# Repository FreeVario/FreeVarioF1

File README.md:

## Welcome to FreeVario

Freevario is an opensource device to provides telemetry data to any vario based program such as XCSoar or XCTrack via bluetooth or wifi. It is based on de STM32F3 processor. The project includes the board Eagle design and source code.
The current status of the project is beta, it is 100% usable, just some rough edges here and there. Since the paragliding season is active, only bug fixes will be added. 

### Features:

Bluetooth, Serial or USB OTG streaming<br>
Solar charger <br>
Power bank (200mA) <br>
Power passthru from external supply <br>
Interval powerbank<br>
Dual pressure sensor support <br>
Adaptive Vario* <br>
Humidity sensor <br>
Accelerometer<br>
Piezo speaker for vario audio <br>
Serial GPS NMEA <br>
NMEA Output PCProbe, PTAS1 and LXNAV<br>

*Adaptive Vario: The sensitivity filter of the barometric sensors are adapted according to the environment. Eg. On a quiet day your flight will be more stable, causing the filter to become more sensitive to changes, this way you will be able to detect the lighter thermals.

#### Bluetooth, Serial or USB OTG streaming

Multiple options available. You can mount a HM-13 bluetooth module to stream BLE or standard bluetooth. Internal serial port can either be used for a i2c OLED display or as an internal serial port for built-in solutions like a Kobo reader.

#### Solar charger

The on board lipo charger can handle multiple power sources including a solar panel to extend the battery life.

#### Powerbank

A on board powerbank can supply up to 200mA 5V via the USB cable to any connected device. When the device is connected to a charger, it will activate a pass through circuit so that the connected device is also charged. This way, disconnecting the usb cable won’t be necessary.
Another option is interval power supply. This will deliver 1 minute out of 5 minutes to the connected device. Most devices won’t support this however. You will need a custom kernel for some Android devices. But is does work with Kobo devices and XCSoar (Top Hat) or LK8000.

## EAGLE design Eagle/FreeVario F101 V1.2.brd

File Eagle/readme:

Eagle files for the FreeVario board

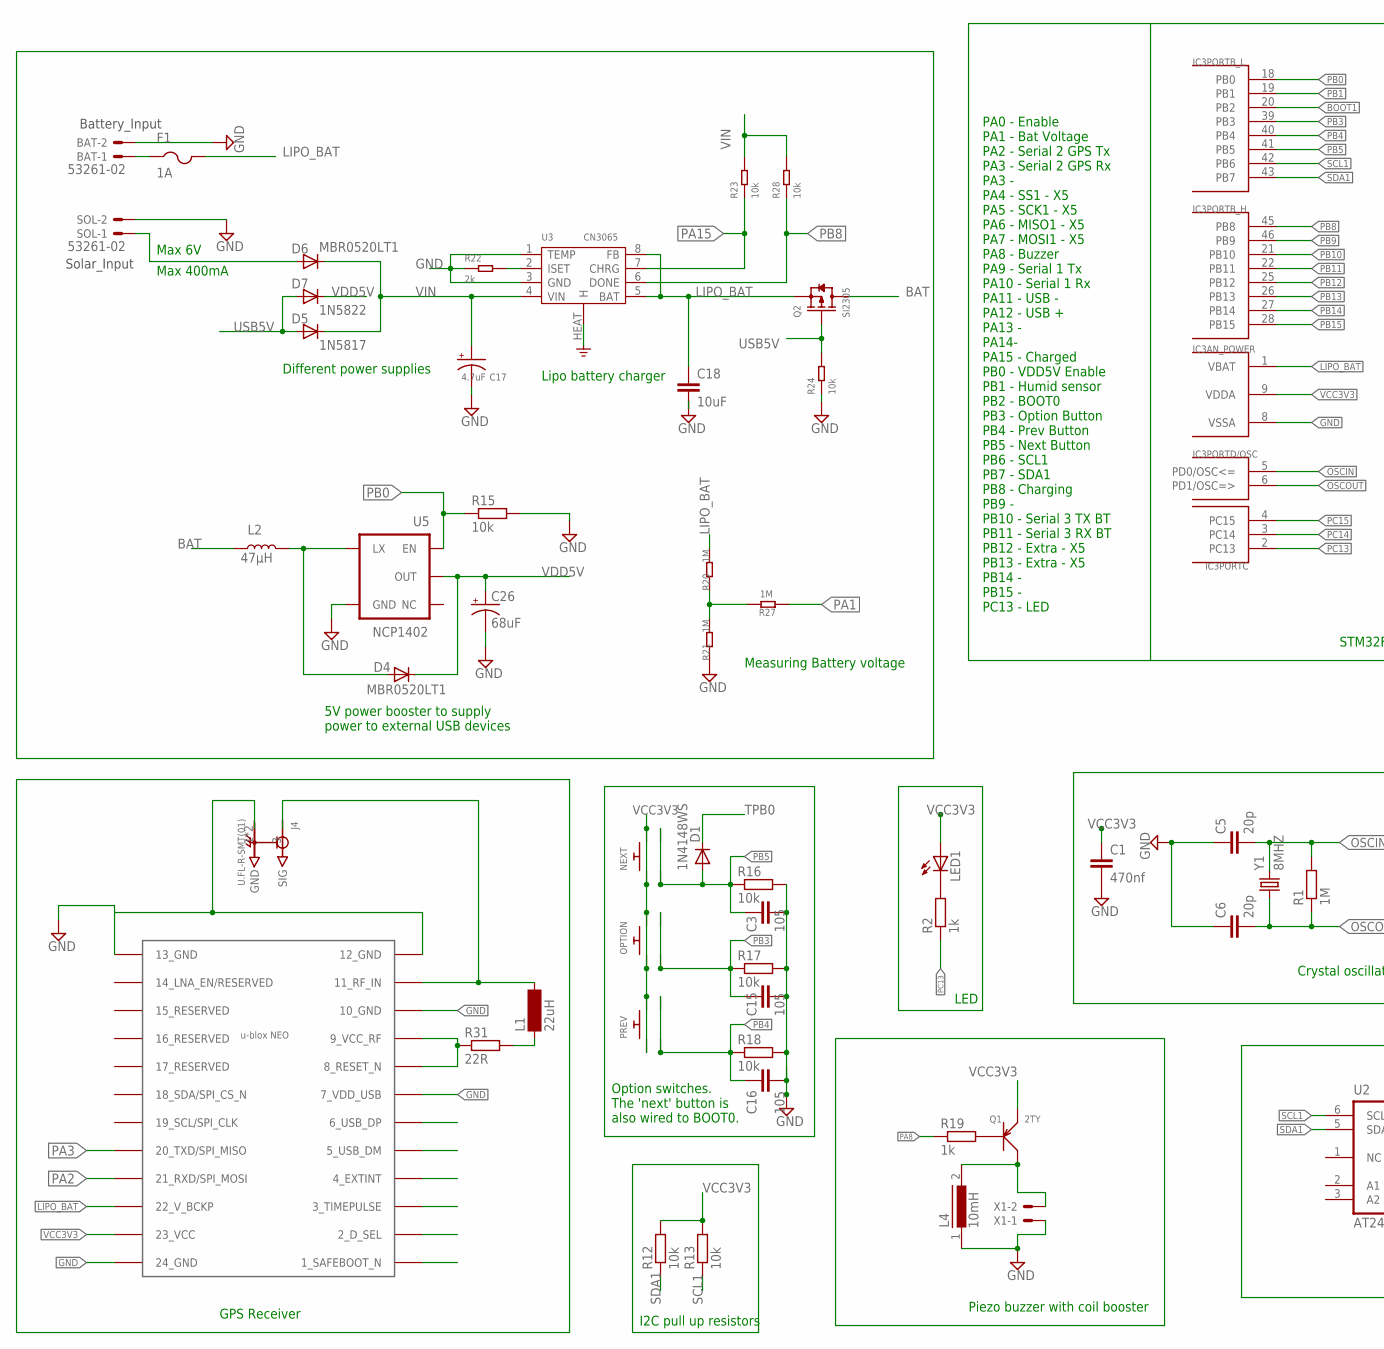
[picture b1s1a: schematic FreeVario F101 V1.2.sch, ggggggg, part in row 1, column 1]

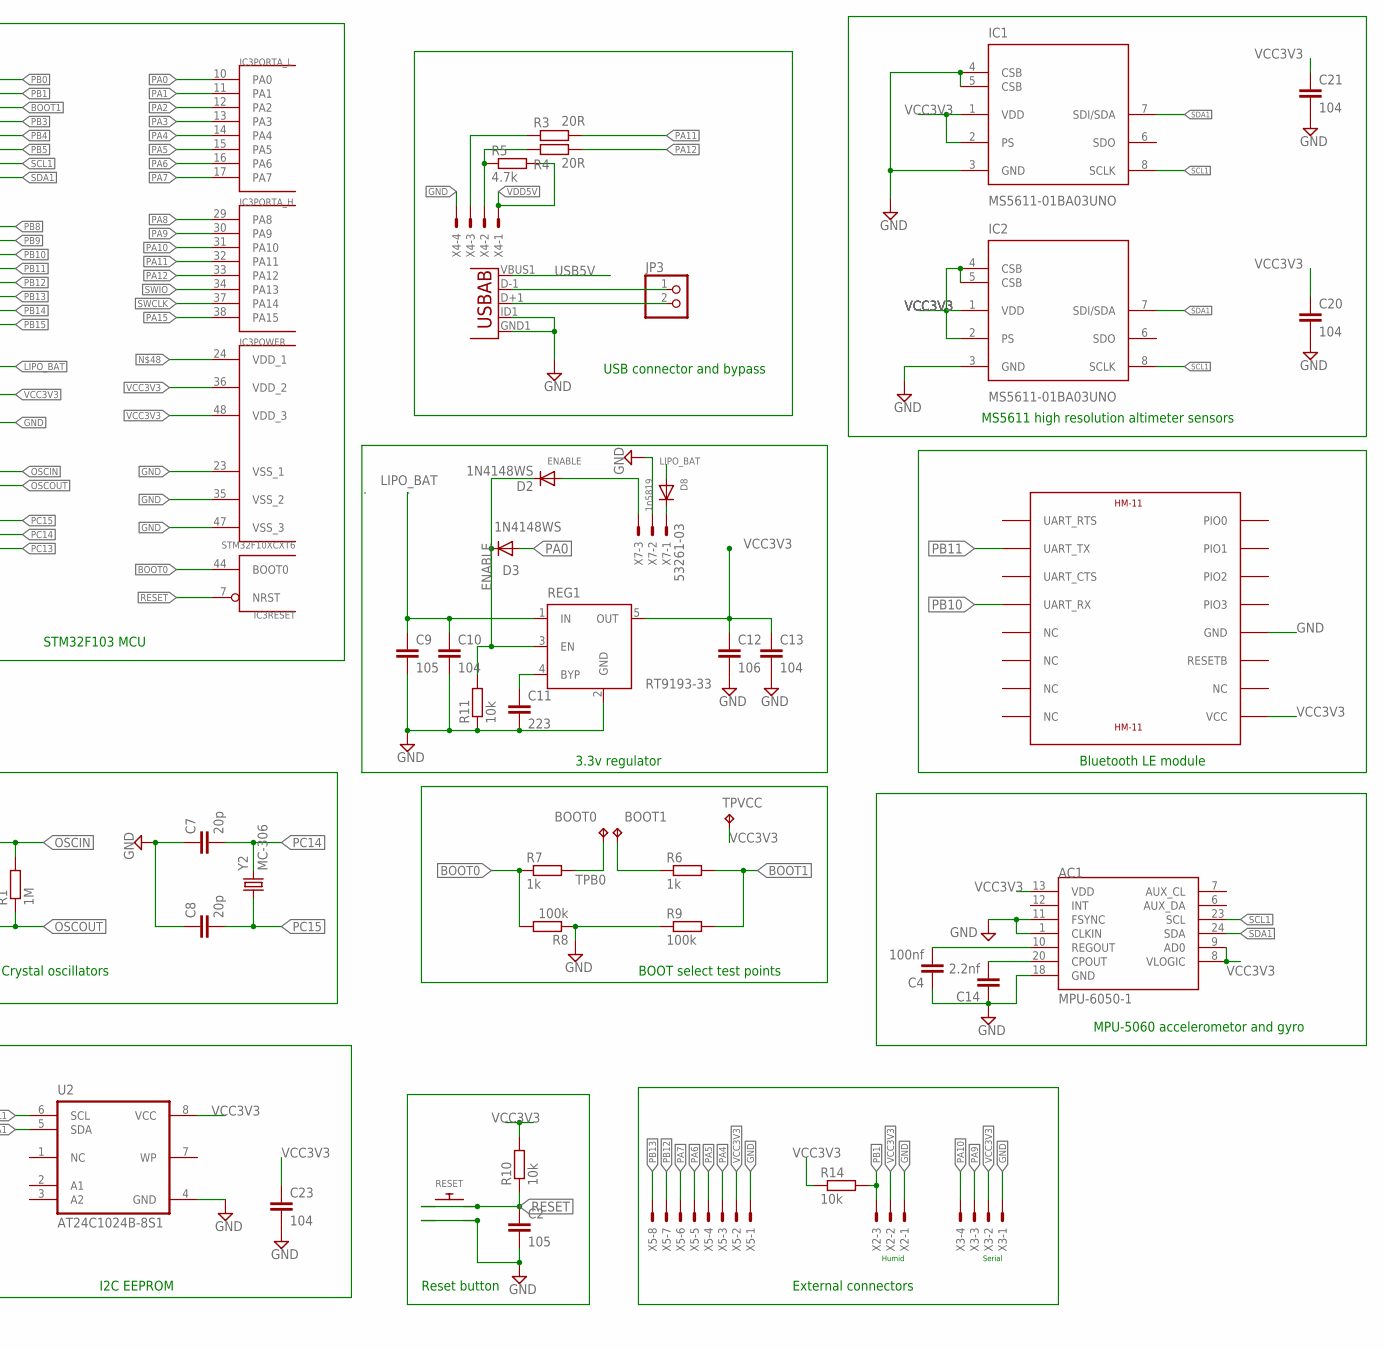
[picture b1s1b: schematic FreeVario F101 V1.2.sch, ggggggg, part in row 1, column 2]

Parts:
AC1: MPU-6050-1; QFN-24-4MM2
BAT: 53261-02
BOOT0, BOOT1: TPTP08R; TP08R
C1: 470nf; C0603K
C2, C3, C15, C16: 105; C0603
C4: 100nf; C0603K
C5, C6, C7, C8: 20p; C0603K
C9: 105; C0603K
C10, C13, C20, C21, C23: 104; C0603K
C11: 223; C0603K
C12: 106; C0603K
C14: 2.2nf; C0603K
C17: 4.7uF; EIA3216
C18: 10uF; C0805
C26: 68uF; EIA3528
D1, D2, D3: 1N4148WS; SOD323-R
D4, D6: MBR0520LT1; SOD-123
D5: 1N5817; SOD-123
D7: 1N5822; DO-214AC
D8: 1n5819; SOD-123
F1: 1A; R1206
HM13: HM-11
IC1, IC2: MS5611-01BA03UNO; SON125P300X500X100-8N
IC3: STM32F10XCXT6; TQFP48
J4: U.FL-R-SMT(01); HRS_U.FL-R-SMT(01)
JP3: PINHD-1X2; 1X02
L1: 22uH; SM-1206
L2: 47µH; CR54
L4: 10mH; MMICC7
LED1: LEDCHIP-LED0603; CHIP-LED0603
NEXT: TS-015A
OPTION: TS-015A
PREV: TS-015A
Q1: 2TY; SOT-23
Q2: SI2305; SOT-23
R1: 1M; R0603
R2, R6, R7, R19: 1k; R0603
R3, R4: 20R; R0603
R5: 4.7k; R0603
R8, R9: 100k; R0603
R10, R11, R12, R13, R14, R15, R16, R17, R18, R23, R24, R28: 10k; R0603
R20, R21, R27: 1M; 0603
R22: 2k; R0603
R31: 22R; R0603
REG1: RT9193-33; SOT23-5
RESET: TS-015A
SOL: 53261-02
TPVCC: TPTP08SQ; TP08SQ
U1: USB""; USB-MICRO-SMD
U2: AT24C1024B-8S1; SO08-8S1
U3: CN3065; DFN-8
U4: NEO-M8
U5: NCP1402; SOT23-5
X1: 53261-02
X2, X7: 53261-03
X3, X4: 53261-04
X5: 53261-08
Y1: 8MHZ; SM49
Y2: MC-306

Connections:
BAT: L2.P$1 (1), Q2.3 (D)
BOOT0: IC3.44 (BOOT0), R7.1, R8.2
BOOT1: IC3.20 (PB2), R6.2, R9.2
ENABLE: D2.C, D3.C, R11.2, REG1.3 (EN)
GND: AC1.1 (CLKIN), AC1.11 (FSYNC), AC1.18 (GND), BAT.2, C1.2, C2.2, C3.2, C4.1, C5.1, C6.1, C7.1, C8.1, C9.2, C10.2, C11.2, C12.2, C13.2, C14.1, C15.2, C16.2, C17.-, C18.2, C20.2, C23.2, C26.C (-), HM13.GND, IC1.3 (GND), IC1.4 (CSB), IC1.5 (CSB), IC2.3 (GND), IC3.8 (VSSA), IC3.23 (VSS_1), IC3.35 (VSS_2), IC3.47 (VSS_3), J4.1 (GND), J4.2 (GND), L4.1, R8.1, R9.1, R11.1, R15.2, R16.2, R17.2, R18.2, R21.1, R22.1, R24.1, REG1.2 (GND), RESET.P$2, RESET.P$4, SOL.2, U1.GND1 (GND), U1.ID1 (USBID), U2.4 (GND), U3.1 (TEMP), U3.3 (GND), U3.HEAT (H), U4.7 (7_VDD_USB), U4.10 (10_GND), U4.12 (12_GND), U4.13 (13_GND), U4.24 (24_GND), U5.4 (GND), X1.1, X2.1, X3.1, X4.4, X5.1, X7.2
LIPO_BAT: C9.1, C10.1, C18.1, D8.A, F1.2, IC3.1 (VBAT), Q2.2 (S), R20.2, REG1.1 (IN), U3.5 (BAT), U3.8 (FB), U4.22 (22_V_BCKP)
unnamed: D8.C, X7.1
unnamed: LED1.C, R2.2
unnamed: C11.1, REG1.4 (BYP)
unnamed: R3.1, X4.3
unnamed: R4.1, R5.1, X4.2
unnamed: BAT.1, F1.1
unnamed: BOOT1.TP, R6.1
unnamed: R20.1, R21.2, R27.2
unnamed: D2.A, X7.3
unnamed: Q1.1 (B), R19.2
unnamed: D6.A, SOL.1
unnamed: AC1.10 (REGOUT), C4.2
unnamed: R22.2, U3.2 (ISET)
unnamed: AC1.20 (CPOUT), C14.2
unnamed: L4.2, Q1.3 (C), X1.2
unnamed: JP3.1, U1.D-1 (D-)
unnamed: JP3.2, U1.D+1 (D+)
unnamed: D4.A, L2.P$2 (2), U5.5 (LX)
unnamed: J4.3 (SIG), L1.2, U4.11 (11_RF_IN)
unnamed: L1.1, R31.2
unnamed: R31.1, U4.8 (8_RESET_N), U4.9 (9_VCC_RF)
OSCIN: C5.2, IC3.5 (PD0/OSC<=), R1.2, Y1.2
OSCOUT: C6.2, IC3.6 (PD1/OSC=>), R1.1, Y1.1
PA0: D3.A, IC3.10 (PA0)
PA1: IC3.11 (PA1), R27.1
PA2: IC3.12 (PA2), U4.21 (21_RXD/SPI_MOSI)
PA3: IC3.13 (PA3), U4.20 (20_TXD/SPI_MISO)
PA4: IC3.14 (PA4), X5.3
PA5: IC3.15 (PA5), X5.4
PA6: IC3.16 (PA6), X5.5
PA7: IC3.17 (PA7), X5.6
PA8: IC3.29 (PA8), R19.1
PA9: IC3.30 (PA9), X3.3
PA10: IC3.31 (PA10), X3.4
PA11: IC3.32 (PA11), R3.2
PA12: IC3.33 (PA12), R4.2
PA15: IC3.38 (PA15), R23.1, U3.7 (CHRG)
PB0: IC3.18 (PB0), R15.1, U5.1 (EN)
PB1: IC3.19 (PB1), R14.2, X2.3
PB3: C15.1, IC3.39 (PB3), OPTION.P$2, OPTION.P$4, R17.1
PB4: C16.1, IC3.40 (PB4), PREV.P$2, PREV.P$4, R18.1
PB5: C3.1, D1.A, IC3.41 (PB5), NEXT.P$2, NEXT.P$4, R16.1
PB8: IC3.45 (PB8), R28.1, U3.6 (DONE)
PB9: IC3.46 (PB9)
PB10: HM13.UART_RX, IC3.21 (PB10)
PB11: HM13.UART_TX, IC3.22 (PB11)
PB12: IC3.25 (PB12), X5.7
PB13: IC3.26 (PB13), X5.8
PB14: IC3.27 (PB14)
PB15: IC3.28 (PB15)
PC13: IC3.2 (PC13), R2.1
PC14: C7.2, IC3.3 (PC14), Y2.4 (2)
PC15: C8.2, IC3.4 (PC15), Y2.1
RESET: C2.1, IC3.7 (NRST), R10.1, RESET.P$1, RESET.P$3
SCL1: AC1.23 (SCL), IC1.8 (SCLK), IC2.8 (SCLK), IC3.42 (PB6), R13.1, U2.6 (SCL)
SDA1: AC1.24 (SDA), IC1.7 (SDI/SDA), IC2.7 (SDI/SDA), IC3.43 (PB7), R12.1, U2.5 (SDA)
SWCLK: IC3.37 (PA14)
SWIO: IC3.34 (PA13)
TPB0: BOOT0.TP, D1.C, R7.2
USB5V: D5.A, D7.A, Q2.1 (G), R24.2, U1.VBUS1 (VBUS)
VCC3V3: AC1.8 (VLOGIC), AC1.9 (AD0), AC1.13 (VDD), C1.1, C12.1, C13.1, C20.1, C21.1, C23.1, HM13.VCC, IC1.1 (VDD), IC1.2 (PS), IC2.1 (VDD), IC2.2 (PS), IC2.4 (CSB), IC2.5 (CSB), IC3.9 (VDDA), IC3.36 (VDD_2), IC3.48 (VDD_3), LED1.A, NEXT.P$1, NEXT.P$3, OPTION.P$1, OPTION.P$3, PREV.P$1, PREV.P$3, Q1.2 (E), R10.2, R12.2, R13.2, R14.1, REG1.5 (OUT), TPVCC.TP, U2.8 (VCC), U4.23 (23_VCC), X2.2, X3.2, X5.2
VDD5V: C26.A (+), D4.C, D7.C, R5.2, U5.2 (OUT), X4.1
VIN: C17.+, D5.C, D6.C, R23.2, R28.2, U3.4 (VIN)

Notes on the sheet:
Serial
Humid
Solar_Input
Battery_Input
PA0 - Enable PA1 - Bat Voltage PA2 - Serial 2 GPS Tx PA3 - Serial 2 GPS Rx PA3 - PA4 - SS1 - X5 PA5 - SCK1 - X5 PA6 - MISO1 - X5 PA7 - MOSI1 - X5 PA8 - Buzzer PA9 - Serial 1 Tx PA10 - Serial 1 Rx PA11 - USB - PA12 - USB + PA13 - PA14- PA15 - Charged PB0 - VDD5V Enable PB1 - Humid sensor PB2 - BOOT0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
Max 400mA
Measuring Battery voltage
5V power booster to supply power to external USB devices
Lipo battery charger
Different power supplies
Max 6V
GPS Receiver
Crystal oscillators
Piezo buzzer with coil booster
External connectors
STM32F103 MCU
Reset button
I2C pull up resistors
Option switches. The 'next' button is also wired to BOOT0.
MS5611 high resolution altimeter sensors
Bluetooth LE module
MPU-5060 accelerometor and gyro
I2C EEPROM
BOOT select test points
3.3v regulator
USB connector and bypass
LED

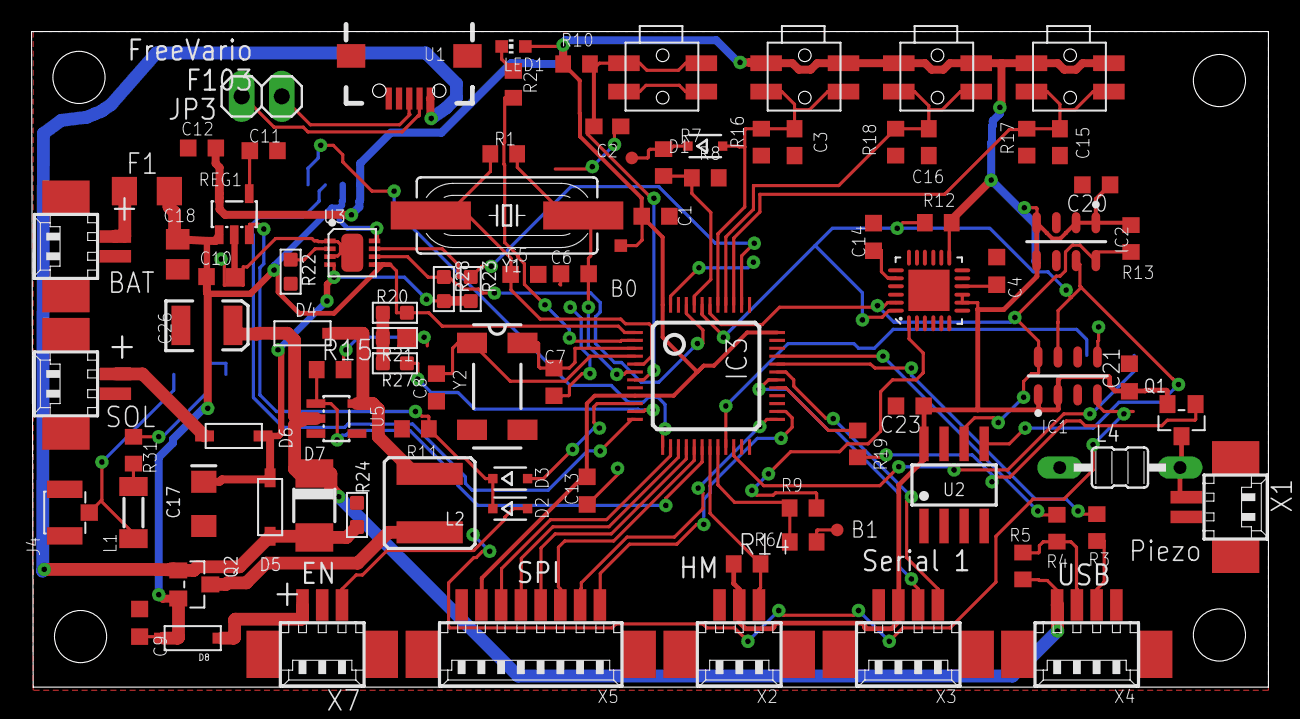
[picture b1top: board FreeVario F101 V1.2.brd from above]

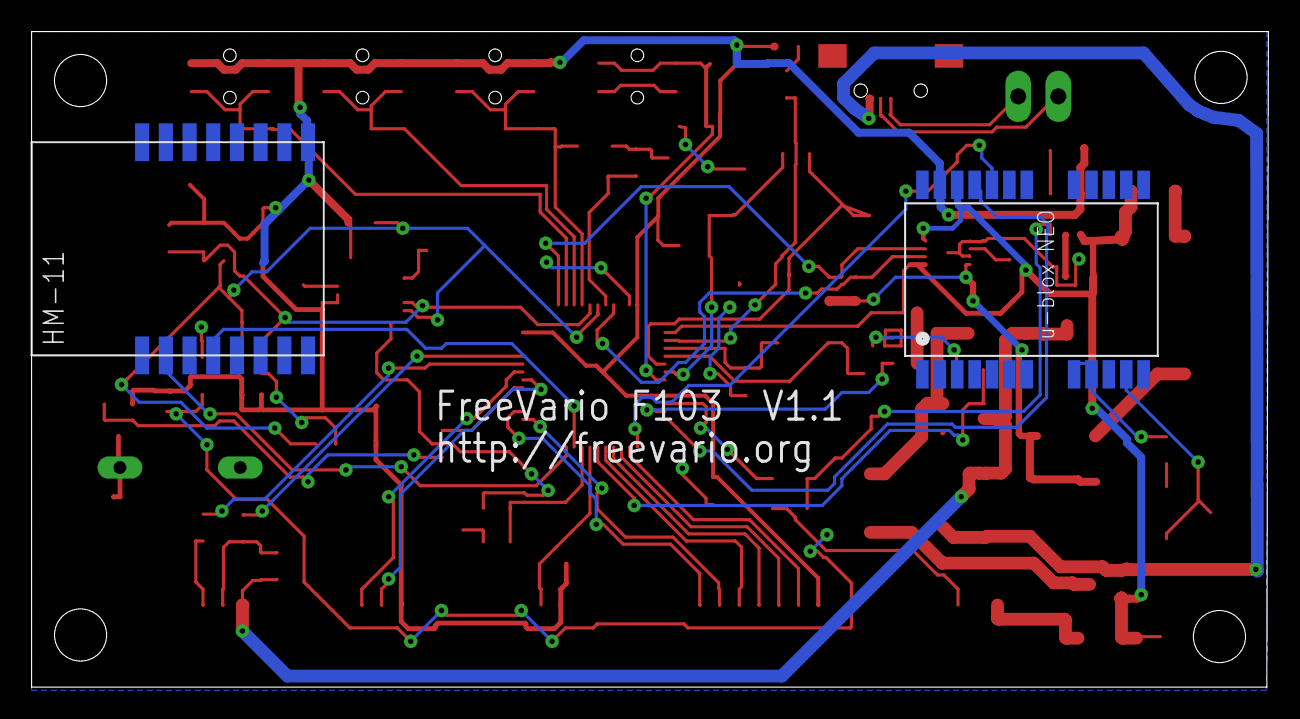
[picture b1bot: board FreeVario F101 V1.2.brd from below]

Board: 2 copper layers, 78.3 x 41.5 mm, 98 parts (2 on the bottom side), 64 nets.

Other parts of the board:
U$1, U$2, U$3, U$4: STAND-OFF

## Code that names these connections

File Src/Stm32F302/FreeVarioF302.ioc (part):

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Mcu.Name=STM32F302C(B-C)Tx
Mcu.Package=LQFP48
Mcu.UserName=STM32F302CBTx
PA10.Mode=I2C
PA10.Signal=I2C2_SDA
PA11.Mode=Device
PA11.Signal=USB_DM
PA12.Mode=Device
PA12.Signal=USB_DP
PA15.Signal=GPIO_Input
PA2.Mode=Asynchronous
PA2.Signal=USART2_TX
PA3.Mode=Asynchronous
PA3.Signal=USART2_RX
PA4.Signal=COMP_DAC1_group
PA8.Signal=S_TIM1_CH1
PA9.Mode=I2C
PA9.Signal=I2C2_SCL
PB0.Signal=GPIO_Output
PB10.Mode=Asynchronous
PB10.Signal=USART3_TX
PB11.Mode=Asynchronous
PB11.Signal=USART3_RX
PB3.Signal=GPXTI3
PB4.Signal=GPXTI4
PB5.Signal=GPXTI5
PB6.Mode=I2C
PB6.Signal=I2C1_SCL
PB7.Mode=I2C
PB7.Signal=I2C1_SDA
PB8.Signal=GPIO_Input
PC13.GPIOParameters=PinState,GPIO_PuPd
PC13.GPIO_PuPd=GPIO_NOPULL
PC13.PinState=GPIO_PIN_SET
PC13.Signal=GPIO_Output
PC14-OSC32_IN.Mode=LSE-External-Oscillator
PC14-OSC32_IN.Signal=RCC_OSC32_IN
PC15-OSC32_OUT.Mode=LSE-External-Oscillator
PC15-OSC32_OUT.Signal=RCC_OSC32_OUT
PF0-OSC_IN.Mode=HSE-External-Oscillator
PF0-OSC_IN.Signal=RCC_OSC_IN
PF1-OSC_OUT.Mode=HSE-External-Oscillator
PF1-OSC_OUT.Signal=RCC_OSC_OUT
RCC.HSEPLLFreq_Value=8000000
RCC.HSE_VALUE=8000000
RCC.SYSCLKFreq_VALUE=72000000
RCC.SYSCLKSourceVirtual=RCC_SYSCLKSOURCE_PLLCLK
board=FreeVarioF302

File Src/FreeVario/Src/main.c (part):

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        * Output
        * EVENT_OUT
        * EXTI
     PA5   ------> SPI1_SCK
     PA6   ------> SPI1_MISO
     PA7   ------> SPI1_MOSI
*/
static void MX_GPIO_Init(void)
{
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  GPIO_InitStruct.Speed = GPIO_SPEED_FREQ_LOW;
  HAL_GPIO_Init(GPIOE, &GPIO_InitStruct);

  /*Configure GPIO pins : B1_Pin PA15 */
  GPIO_InitStruct.Pin = B1_Pin|GPIO_PIN_15;
  GPIO_InitStruct.Mode = GPIO_MODE_INPUT;
  GPIO_InitStruct.Pull = GPIO_NOPULL;
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  GPIO_InitStruct.Alternate = GPIO_AF5_SPI1;
  HAL_GPIO_Init(GPIOA, &GPIO_InitStruct);

  /*Configure GPIO pin : PB0 */
  GPIO_InitStruct.Pin = GPIO_PIN_0;
  GPIO_InitStruct.Mode = GPIO_MODE_OUTPUT_PP;
  GPIO_InitStruct.Pull = GPIO_NOPULL;
  GPIO_InitStruct.Speed = GPIO_SPEED_FREQ_LOW;
  HAL_GPIO_Init(GPIOB, &GPIO_InitStruct);

  /*Configure GPIO pins : PB3 PB4 PB5 */
  GPIO_InitStruct.Pin = GPIO_PIN_3|GPIO_PIN_4|GPIO_PIN_5;
  GPIO_InitStruct.Mode = GPIO_MODE_IT_RISING;
  GPIO_InitStruct.Pull = GPIO_NOPULL;
  HAL_GPIO_Init(GPIOB, &GPIO_InitStruct);

  /*Configure GPIO pin : PB8 */
  GPIO_InitStruct.Pin = GPIO_PIN_8;
  GPIO_InitStruct.Mode = GPIO_MODE_INPUT;
  GPIO_InitStruct.Pull = GPIO_NOPULL;
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
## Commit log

2017-10-05 Set theme jekyll-theme-slate
2017-10-05 Create CNAME
2017-10-05 Update setupc9
2017-10-17 Started porting from XCSensors
2017-10-22 Added all devices
2017-10-23 removed timer function from DHT
2017-10-23 fixed time problem
2017-10-29 Ported the Audio interface
2017-11-03 Eagle Files
2017-12-17 Added bill of material
2018-02-09 Initial
2018-02-09 Structure test
2018-02-10 Moved Config_hal
2018-02-10 Added HAL timers and buzzer
2018-02-10 Update Gitignore
2018-02-10 Clean Master Brache
2018-02-10 Cleanup
2018-02-11 Added settings and baro sequence
2018-02-11 Baro sensors
2018-02-11 Switched from stack to queue
2018-02-11 Commit from branche
2018-02-13 Added Baro and tone processing
2018-02-15 Added audio timers
2018-02-18 Switched back to old tone generation. Added DAC DAM audio
2018-02-19 Fixed audio stuttering
2018-02-25 Merged from discovery branche
2018-03-03 Updated to new HAL firmware
2018-03-03 Switched to main branche
2018-03-03 Added Setup doc
2018-03-04 Code cleanup
2018-03-04 Added C linker comment
2018-03-04 Added IWGD. Improved ms5611 i2C connectivity.
2018-03-04 More relaxed watchdog
2018-03-05 Added I2C helper in place of weird value watchdog
2018-03-05 Added bus reset to baro value overload
2018-03-06 Added data valid flag
2018-03-08 Improved stability. Buffer overrun prevention.
2018-03-11 Imroved I2C stability
2018-03-11 Added check for erratic values
2018-03-11 Added OLED support
2018-03-11 Removed MBED version
2018-03-12 Started with seperate display control
2018-03-13 Expanded display windows
2018-03-13 Started with buttons
2018-03-14 Added prev next button. 1st milestone reached.
2018-03-18 Added Extra board
2018-03-20 Corrected Vario calculation.
2018-03-21 Reduced data rate.
2018-03-28 Fixed c-probe NMEA sentence
2018-03-30 Moved internal io to seperate file. Added powerbank function.
2018-03-31 Added interval powerbank option. Most devices probably won't support it.
2018-04-01 Fixed OLED problem
2018-04-01 Added battery %
2018-04-01 Fixed NMEA sentence battery %
2018-04-01 Added STM32F302
2018-04-02 Added display refresh option
2018-04-02 Small correction for the mpu6050 adress pin
2018-04-02 Added low pass filter
2018-04-08 Added Startup tone
2018-04-08 Added USB reset command
2018-05-06 Moved config.h to Src folder
2018-05-13 Added pre-compiled definitions
2018-05-27 Added option to disable powerbank function at startup
2018-06-09 Added power save function for the OLED screen
2018-06-20 Added display update disable

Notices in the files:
Src/FreeVario/Src/main.c:
Copyright (c) 2018 STMicroelectronics International N.V.
All rights reserved.
(C) COPYRIGHT STMicroelectronics *****END OF FILE
parts and their libraries:
SparkFun-Hardware: Licensing: Creative Commons ShareAlike 4.0 International - https://creativecommons.org/licenses/by-sa/4.0
memory-atmel: Copyright (C) 2008, Bob Starr
